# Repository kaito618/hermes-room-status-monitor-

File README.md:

# hermes-room-status-monitor-
i'm making a device to monitor my room's temp and humidity 

schematic done
i chose what sensor i want to use i'll use the SHT31-DIS-B2.5KS to make a room temp and hum monitor

added 2 buttons to control the device and an oled screen to show room status

schematic

done w pcb kicad 
im having some real issues with my footprints and my kicad ill be posting the pcb pic later on when i fix everything

MY KICAD DIED guess my 18 yr old laptop didn't wanna take it anymore or maybe it's linux gon no clue anyways after hours of debegguing i switched to easyeda adn redid averything

pcb done easyeda
i finished the pcb layout and wiring and getting my 3d models ready

3d model 

## 🛠 Bill of Materials (BOM)

| Component | Description | Qty | Est. Price (EGP) | Source / Link |
| :--- | :--- | :---: | :--- | :--- |
| **Microcontroller** | Seeed Studio XIAO RP2040 | 1 | 499 | [amazoneg](https://www.amazon.eg/-/en/gp/product/B0GHNR74YH/ref=ewc_pr_img_2?smid=A1FZS2ISSCLNWQ&psc=1) |
| **Sensor** | SHT31 High-Precision Temp & Humidity ($I^2C$) | 1 | 195.00 | [RAM Electronics](https://www.ram-e-shop.com/shop/kit-sht31-sht31-temperature-humidity-sensor-module-9216) |
| **Display** | 0.96" OLED 128x64 ($I^2C$ SSD1306) | 1 | 160.00 | [RAM Electronics](https://www.ram-e-shop.com/shop/oled-0-96-4pin-oled-0-96-4pin-lcd-display-module-i2c-iic-communicate-7772) |
| **Buttons** | mx switches (THT) | 2 | 175 | [amazoneg](https://www.amazon.eg/-/en/gp/product/B0GRPPX2T6/ref=ewc_pr_img_1?smid=A209IF81KPKFRD&psc=1) |
| **Resistors** | 10k Ohm 1/4W (Pull-ups for $I^2C$) | 2 | 4 | [RAM Electronics](https://www.ram-e-shop.com/shop/carbon-resistance-1-4w-price-per-4-resistors-9506#attr=301) |
| **capacitors** | 2.54mm Female Header Strip (1x40) | 2 | 2 | [RAM Electronics](https://www.ram-e-shop.com/shop/c-10u25v-capacitor-10uf-25v-6095) |

| **TOTAL** | **Estimated Project Cost** | | **~1034egp 19.03 usd** | |

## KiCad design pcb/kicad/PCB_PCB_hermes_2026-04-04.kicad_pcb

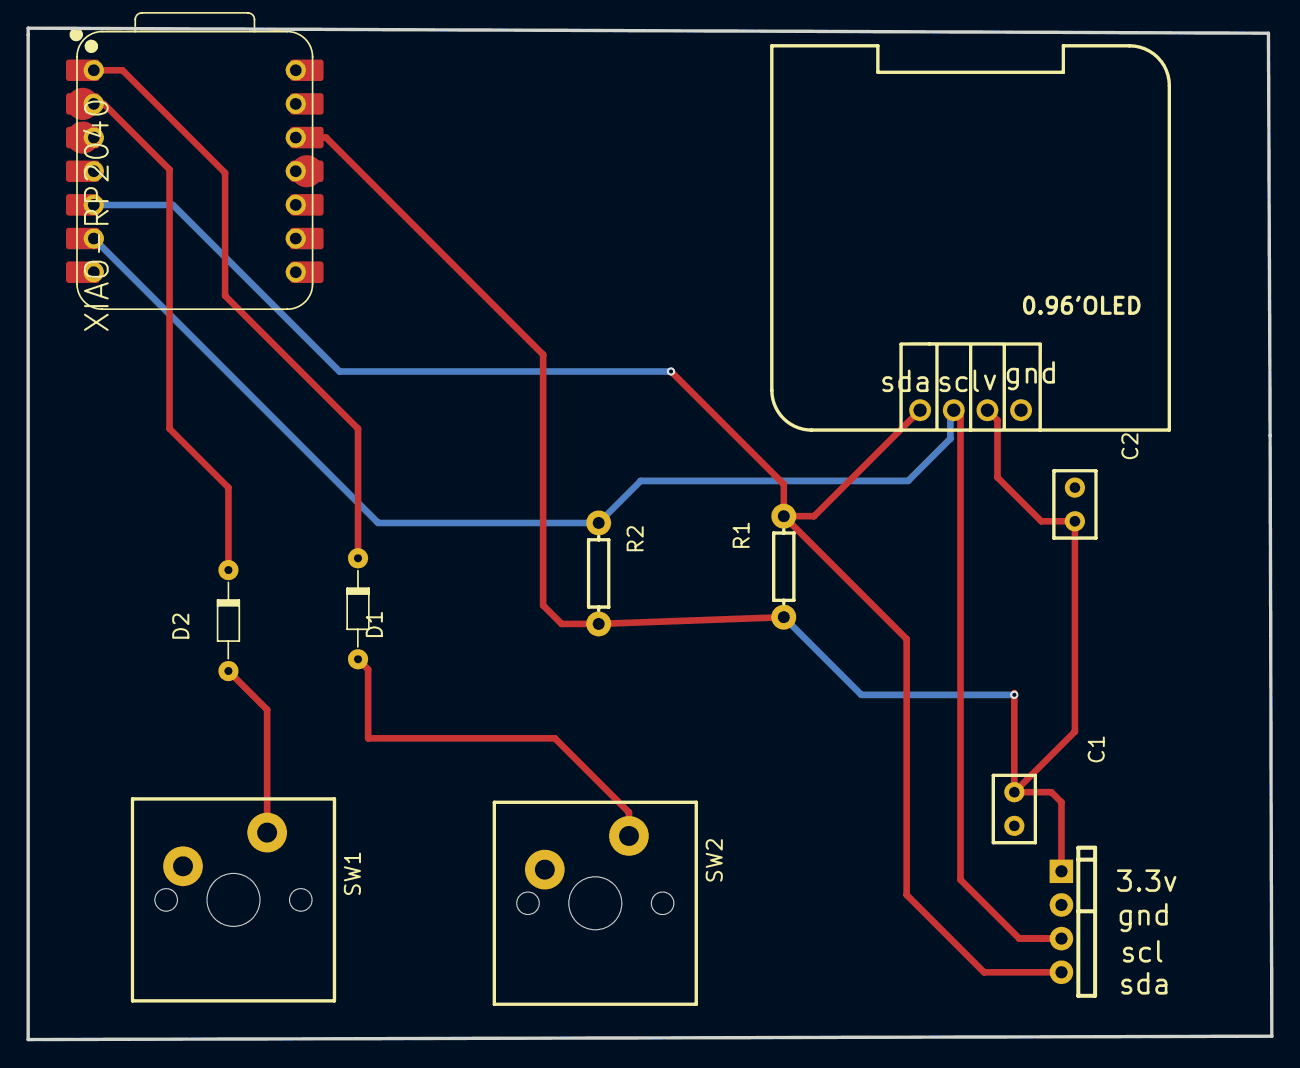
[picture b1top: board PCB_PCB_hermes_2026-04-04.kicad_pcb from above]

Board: 2 copper layers, 93.9 x 76.3 mm, 11 parts (0 on the bottom side), 8 nets.

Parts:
A1: SHT31
C1, C2: 0.1uF; CERAMIC CAPACITOR_100NF
D1, D2: 1N4148; 1N418 PAS 7.62MM
OLED1: 0.96'OLED; 0.96OLED_4P
R1, R2: 4.7k; AXIAL-0.3
SW1, SW2: Switch Cherry MX; SWITCH CHERRY MX
U1: XIAO-RP2040; VARISTOR_XIAO-RP2040-DIP

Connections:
3.3V: A1.1, C1.1, C2.1, OLED1.2, R1.2, R2.2, U1.12
GND: A1.2, C1.2, C2.2, OLED1.1, SW1.1, SW2.1, U1.13
SCL: A1.3, OLED1.3, R2.1, U1.6
SDA: A1.4, OLED1.4, R1.1, U1.5
SW1_2: D2.2, SW1.2
SW2_2: D1.2, SW2.2
U1_1: D1.1, U1.1
U1_2: D2.1, U1.2

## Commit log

2026-04-03 Update README with project progress and details
    Expanded project details including sensor choice, schematic, PCB design updates, and issues faced during development.
2026-04-03 Create s
2026-04-04 Create note
